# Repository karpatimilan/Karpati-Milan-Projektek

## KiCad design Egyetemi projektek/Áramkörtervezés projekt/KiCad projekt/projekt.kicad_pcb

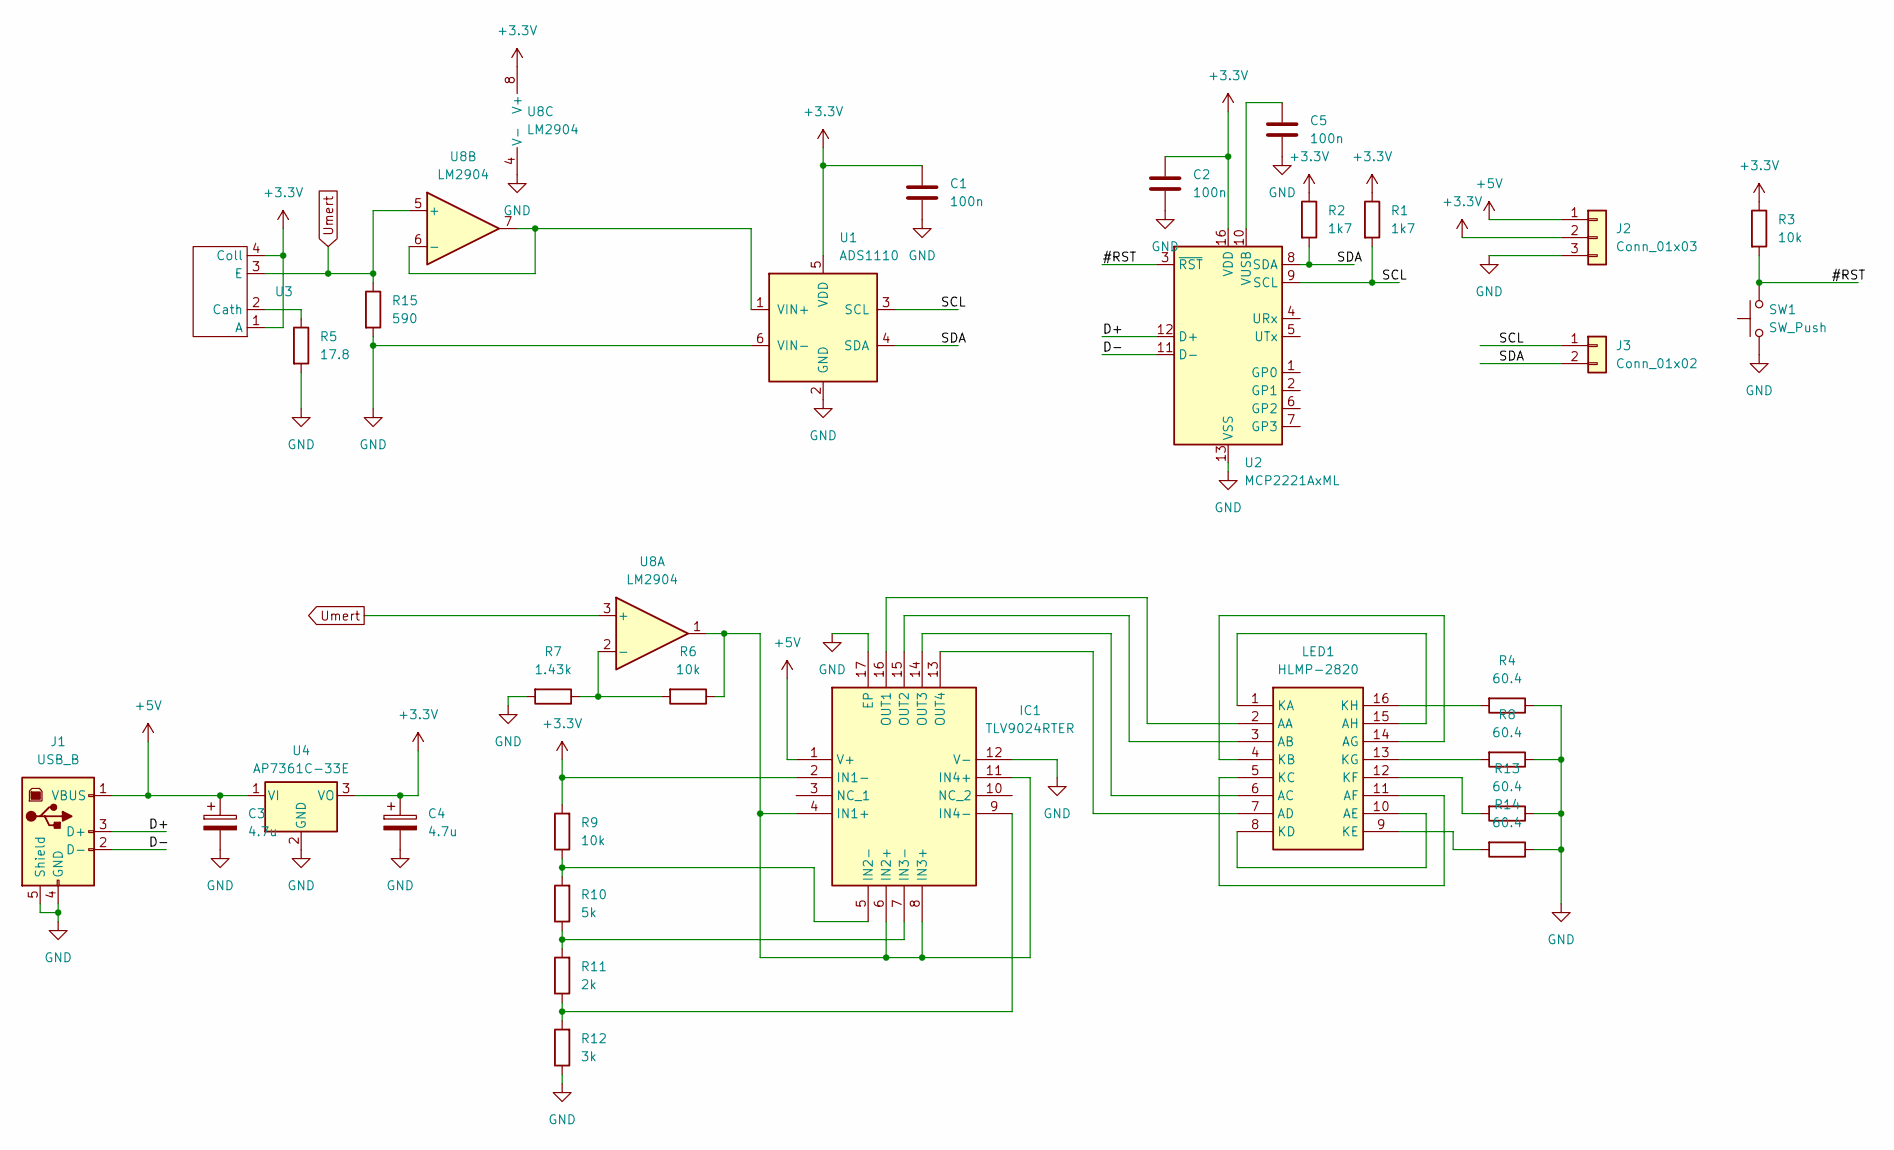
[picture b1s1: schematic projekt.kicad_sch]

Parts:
C1, C2, C5: 100n; C_1206_3216Metric; Manufacturer_Part_Number C1206X104J9RAL7210; Mouser Part Number 80-C1206X104J9RAL721
C3, C4: 4.7u; C_1206_3216Metric; Manufacturer_Part_Number T491A475K006AT7622; Mouser Part Number 80-T491A475K6AT7622
IC1: TLV9024RTER; QFN50P300X300X80-17N-D; Mouser Part Number 595-TLV9024RTER
J1: USB_B; USB_B_Lumberg_2411_02_Horizontal; Manufacturer_Part_Number 61729-1021BLF; Mouser Part Number 649-61729-1021BLF
J2: Conn_01x03; PinHeader_1x03_P2.54mm_Vertical; Mouser Part Number 244112
J3: Conn_01x02; PinHeader_1x02_P2.54mm_Vertical; Mouser Part Number 244112
LED1: HLMP-2820; DIP762W56P254L2032H647Q16N; Mouser Part Number 630-HLMP-2820
R1, R2: 1k7; R_1206_3216Metric; Manufacturer_Part_Number RK73G1JTTD1071C; Mouser Part Number 660-RK73G1JTTD1071C
R3, R6, R9: 10k; R_1206_3216Metric; Manufacturer_Part_Number TNPW120610K0BEEA; Mouser Part Number 71-TNPW120610K0BEEA
R4, R8, R13, R14: 60.4; R_1206_3216Metric; Manufacturer_Part_Number TNPW120660R4BEEA; Mouser Part Number 71-TNPW120660R4BEEA
R5: 17.8; R_1206_3216Metric; Manufacturer_Part_Number TNPW120617R8BEEN; Mouser Part Number 71-TNPW120617R8BEEN
R7: 1.43k; R_1206_3216Metric; Manufacturer_Part_Number TNPW12061K43BEEA; Mouser Part Number 71-TNPW12061K43BEEA
R10: 5k; R_1206_3216Metric; Manufacturer_Part_Number TNPW12065K00BEEA; Mouser Part Number 71-TNPW12065K00BEEA
R11: 2k; R_1206_3216Metric; Manufacturer_Part_Number TNPW12062K00BEEA; Mouser Part Number 71-TNPW12062K00BEEA
R12: 3k; R_1206_3216Metric; Manufacturer_Part_Number TNPW12063K00BEEA; Mouser Part Number 71-TNPW12063K00BEEA
R15: 590; R_1206_3216Metric; Manufacturer_Part_Number ERA-8AEB5900V; Mouser Part Number 667-ERA-8AEB5900V
SW1: SW_Push; SW_SPST_Omron_B3FS-100xP; Manufacturer_Part_Number B3FS-1000P; Mouser Part Number 653-B3FS-1000P
U1: ADS1110; SOT-23-6; Manufacturer_Part_Number ADS1100A1IDBVT; Mouser Part Number 595-ADS1100A1IDBVT
U2: MCP2221AxML; QFN-16-1EP_4x4mm_P0.65mm_EP2.5x2.5mm; Manufacturer_Part_Number MCP2221AT-I/ML; Mouser Part Number 579-MCP2221AT-I/ML
U3: TCRT1010_VIS; Manufacturer_Part_Number TCRT1000; Mouser Part Number 782-TCRT1000
U4: AP7361C-33E; SOT-223-3_TabPin2; Manufacturer_Part_Number AP7361C-33E-13; Mouser Part Number 621-AP7361C-33E-13
U8: LM2904; DIP8_300; Manufacturer_Part_Number LM2904N/NOPB; Mouser Part Number 926-LM2904N/NOPB

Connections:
+3.3V: C1.1, C2.1, C4.1, IC1.2 (IN1-), J2.2, R1.1, R2.1, R3.1, R9.2, U1.5 (VDD), U2.16 (VDD), U3.1 (A), U3.4 (Coll), U4.3 (VO), U8.8 (V+)
+5V: C3.1, IC1.1 (V+), J1.1 (VBUS), J2.1, U4.1 (VI)
/#RST: R3.2, SW1.2, U2.3 (~RST)
/D+: J1.3 (D+), U2.12 (D+)
/D-: J1.2 (D-), U2.11 (D-)
/SCL: J3.1, R1.2, U1.3 (SCL), U2.9 (SCL)
/SDA: J3.2, R2.2, U1.4 (SDA), U2.8 (SDA)
GND: C1.2, C2.2, C3.2, C4.2, C5.2, IC1.12 (V-), IC1.17 (EP), J1.4 (GND), J1.5 (Shield), J2.3, R4.1, R5.2, R7.2, R8.1, R12.1, R13.1, R14.1, R15.2, SW1.1, U1.2 (GND), U1.6 (VIN-), U2.13 (VSS), U4.2 (GND), U8.4 (V-)
unnamed: IC1.4 (IN1+), IC1.6 (IN2+), IC1.8 (IN3+), IC1.11 (IN4+), R6.1, U8.1
unnamed: IC1.5 (IN2-), R9.1, R10.2
unnamed: IC1.7 (IN3-), R10.1, R11.2
unnamed: IC1.9 (IN4-), R11.1, R12.2
unnamed: IC1.16 (OUT1), LED1.2 (AA)
unnamed: IC1.15 (OUT2), LED1.3 (AB)
unnamed: IC1.14 (OUT3), LED1.6 (AC)
unnamed: IC1.13 (OUT4), LED1.7 (AD)
unnamed: LED1.8 (KD), LED1.10 (AE)
unnamed: LED1.5 (KC), LED1.11 (AF)
unnamed: LED1.4 (KB), LED1.14 (AG)
unnamed: LED1.1 (KA), LED1.15 (AH)
unnamed: LED1.9 (KE), R14.2
unnamed: LED1.12 (KF), R13.2
unnamed: LED1.13 (KG), R8.2
unnamed: LED1.16 (KH), R4.2
unnamed: U1.1 (VIN+), U8.6 (-), U8.7
unnamed: C5.1, U2.10 (VUSB)
unnamed: R5.1, U3.2 (Cath)
unnamed: R6.2, R7.1, U8.2 (-)
Umert: R15.1, U3.3 (E), U8.3 (+), U8.5 (+)

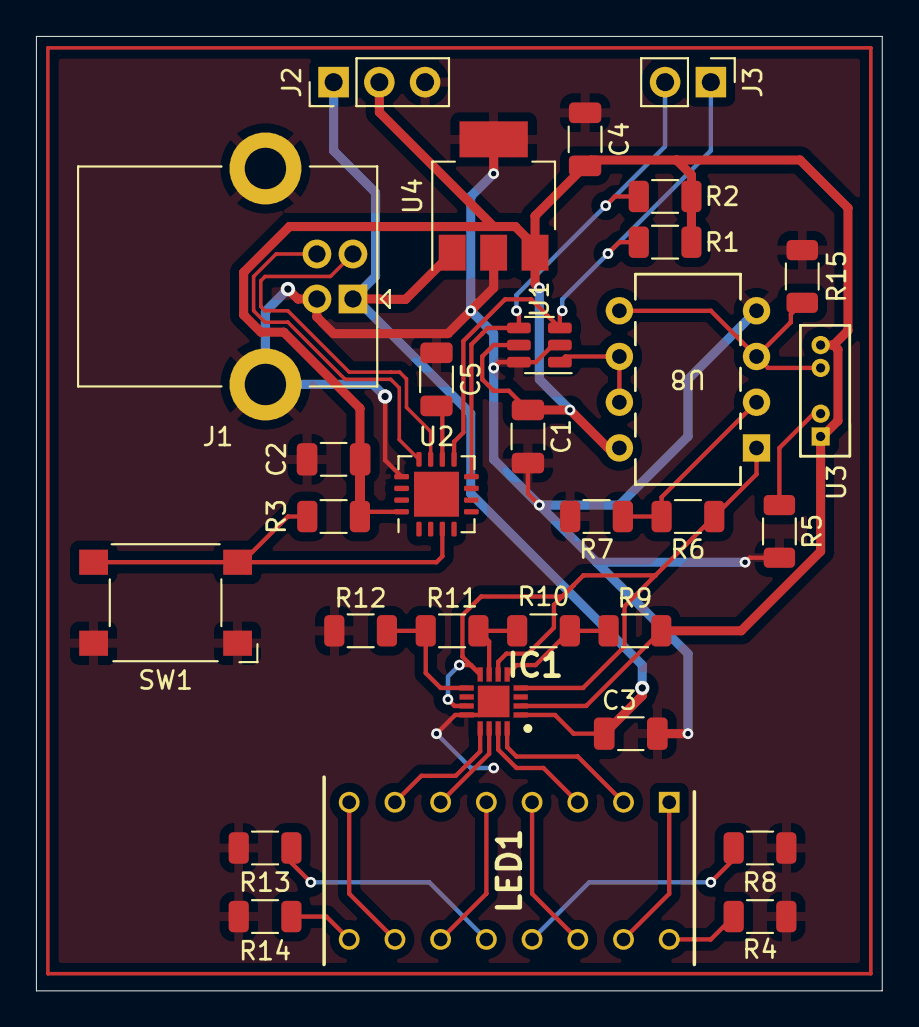
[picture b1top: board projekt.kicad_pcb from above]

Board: 2 copper layers, 47.0 x 53.0 mm, 31 parts (0 on the bottom side), 29 nets.

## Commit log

2024-12-08 szakdolgozat
